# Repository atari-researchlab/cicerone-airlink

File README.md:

<!-- LICENSE INFORMATION
Copyright (C) 2025 ATARI Research Lab
Permission is granted to copy, distribute and/or modify this document
under the terms of the GNU Free Documentation License, Version 1.3
or any later version published by the Free Software Foundation;
with no Invariant Sections, no Front-Cover Texts, and no Back-Cover Texts.
A copy of the license is included in the section entitled "GNU
Free Documentation License".
-->

<!-- markdownlint-disable MD041 MD013 -->

<p align="center">
  Grant <strong><em>PID2021-126810OB-I00</em></strong> funded by:<br />
  <br />
</p>

<p align="center">

</p>

* * *

<!-- markdownlint-enable MD013 -->

# CICERONE AirLink

CICERONE AirLink© is an indoor air quality telemonitoring device designed for the project CICERONE
(*PID2021-126810OB-I00*).

The air quality device operates by transmitting data every ten minutes for all the parameters
collected by the various sensors, thanks to the communication module created in conjunction with the
RTC. This way, if there are no data transmission failures, a total of 144 daily data points are
obtained for each of the parameters collected by the CO2 and PM/VOCs sensors.

## Table of Contents

<!-- markdownlint-disable MD007 -->
- [CICERONE AirLink](#cicerone-airlink)
  - [Table of Contents](#table-of-contents)
  - [🎓 Features](#-features)
  - [📝 Specifications](#-specifications)
  - [📚 Documentation](#-documentation)
  - [📑 Citations](#-citations)
    - [APA](#apa)
    - [BibTeX](#bibtex)
  - [📃 Licences](#-licences)
<!-- markdownlint-enable MD007 -->

## 🎓 Features

- Sensors for measuring particulate matter (PM1, PM2.5, PM4, and PM10), volatile organic compounds
  (VOCs), carbon dioxide (CO2), temperature, and relative humidity.
- Clock for synchronizing sensor data readings and configuring the data packets to be transmitted.
- Autonomous data transmission independent of the user via an NB-IoT communication module. The
  device includes its own SIM card for sending average sensor values every ten minutes.
- Energy autonomy of up to 5 hours of operation on a fully charged battery.
- Optional cough detection feature using a machine learning algorithm. The device can count the
  number of cough events within a desired time frame.

[Back to top](#top)

## 📝 Specifications

- Electronics
    - Microcontroller
        - Arduino Nano 33 BLE Sense Rev2
    - Sensors
        - PM/VOC
        - CO2
        - Temperature
        - Ambient relative humidity
    - I/O
        - Power switch
    - Communication
        - NB-IoT module (SIM7020G)
    - Others
        - 2-layer custom PCB
        - RTC
        - 900 mAh Lithium-ion battery
        - 5V@1A AC-DC adapter
- Mechanics
    - 3D-printed case
    - Developed in SOLIDWORKS® 2020
- Firmware
    - Sends the data to a server containing 10 minutes average measurements of all sensors via the
      NB-IoT module.
    - Developed in Arduino IDE

[Back to top](#top)

## 📚 Documentation

- [Documentation](https://atari-researchlab.github.io/cicerone-airlink/)
- [Description](https://atari-researchlab.github.io/cicerone-airlink/description/)
    - [Electronics](https://atari-researchlab.github.io/cicerone-airlink/description/electronics/)
    - [Firmware](https://atari-researchlab.github.io/cicerone-airlink/description/firmware/)
- [User guide](https://atari-researchlab.github.io/cicerone-airlink/user-guide/)
    - [Assembly](https://atari-researchlab.github.io/cicerone-airlink/user-guide/assembly/)
    - [Firmware customization](https://atari-researchlab.github.io/cicerone-airlink/user-guide/firmware-configuration/)

[Back to top](#top)

## 📑 Citations

Please consider citing our papers in your publications if the project helps your research.

### APA

``` text
[1] Camacho-Magriñán, P.; Sales-Lerida, D.; León-Jiménez, A.; Sanchez-Morillo, D. Indoor
Environmental Monitoring and Chronic Respiratory Diseases: A Systematic Review. Technologies 2025,
13, 122. https://doi.org/10.3390/technologies13030122
```

``` text
[2] P. Camacho Magriñan, D. Sales Lerida, R. Moreno Mellado, A. Lara Doña, & D. Sánchez Morillo.
(2024). Sistema de telemonitorización de la calidad de aire interior para pacientes con EPOC. XLII
Congreso Anual de la Sociedad Española de Ingeniería Biomédica. CASEIB 2024, 89-92.
```

### BibTeX

``` bibtex
@Article{technologies13030122,
AUTHOR = {Camacho-Magriñán, Patricia and Sales-Lerida, Diego and León-Jiménez, Antonio and
Sanchez-Morillo, Daniel},
TITLE = {Indoor Environmental Monitoring and Chronic Respiratory Diseases: A Systematic Review},
JOURNAL = {Technologies},
VOLUME = {13},
YEAR = {2025},
NUMBER = {3},
ARTICLE-NUMBER = {122},
URL = {https://www.mdpi.com/2227-7080/13/3/122},
ISSN = {2227-7080},
DOI = {10.3390/technologies13030122}
}
```

``` bibtex
@inproceedings{6842c68c8a34bb2df9fc79a9,
title={Sistema de telemonitorización de la calidad de aire interior para pacientes con EPOC},
ISBN={978-84-09-67332-2},
booktitle={XLII Congreso Anual de la Sociedad Española de Ingeniería Biomédica. CASEIB 2024},
publisher={Sociedad Española de Ingeniería Biomédica (SEIB)},
author={P. Camacho Magriñan and D. Sales Lerida and R. Moreno Mellado and A. Lara Doña and D.
Sánchez Morillo},
year={2024},
pages={89-92}
}
```

[Back to top](#top)

## 📃 Licences

All hardware materials and designs, firmware and documentation provided here are licenced under the
following licenses:
<!-- markdownlint-disable MD013 -->
- Hardware: <a href="/hardware/LICENSE.md" target="_blank"> CERN Open Hardware Licence Version 2 - Strongly Reciprocal</a>
- Firmware source code: <a href="firmware/LICENSE.md" target="_blank"> GNU General Public License version 3 or later</a>
- Documentation: <a href="/docs/LICENSE.md" target="_blank"> GNU Free Documentation License, Version 1.3 or later</a>

[Back to top](#top)

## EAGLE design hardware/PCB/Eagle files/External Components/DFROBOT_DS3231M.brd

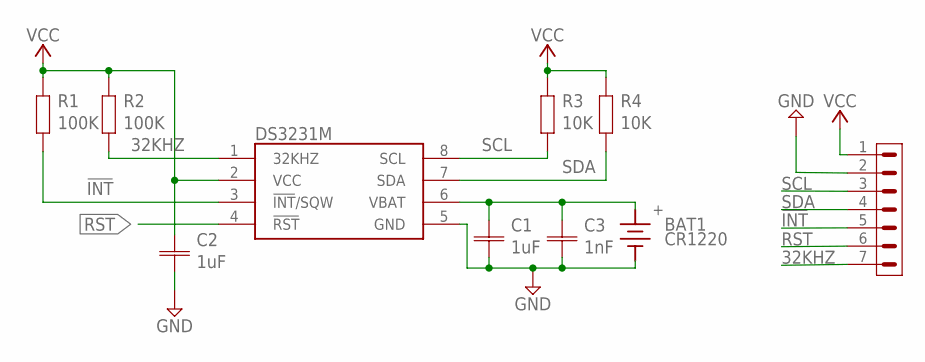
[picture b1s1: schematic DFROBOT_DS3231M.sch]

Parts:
BAT1: CR1220; S8411-45R
C1, C2: 1uF; CAPC1005X60
C3: 1nF; CAPC1005X60
DS3231M: DS3231MZ+; SOIC127P600X175-8N
JP1: PINHD-1X7; DS3231M_HEADER
R1, R2: 100K; RESC1005X40
R3, R4: 10K; RESC1005X40

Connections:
32KHZ: DS3231M.1 (32KHZ), JP1.7, R2.2
!INT: DS3231M.3 (!INT!/SQW), JP1.5, R1.2
GND: BAT1.1 (-), C1.2, C2.2, C3.2, DS3231M.5 (GND), JP1.2
RST: DS3231M.4 (!RST), JP1.6
SCL: DS3231M.8 (SCL), JP1.3, R3.2
SDA: DS3231M.7 (SDA), JP1.4, R4.2
VBAT: BAT1.2 (+), C1.1, C3.1, DS3231M.6 (VBAT)
VCC: C2.1, DS3231M.2 (VCC), JP1.1, R1.1, R2.1, R3.1, R4.1

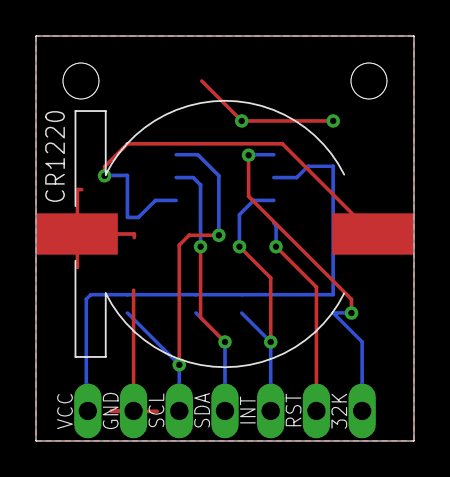
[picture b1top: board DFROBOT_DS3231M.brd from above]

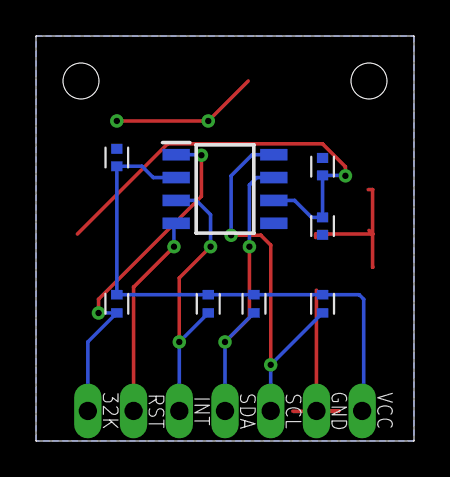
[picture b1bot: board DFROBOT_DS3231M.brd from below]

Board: 2 copper layers, 21.0 x 22.5 mm, 10 parts (8 on the bottom side), 8 nets.

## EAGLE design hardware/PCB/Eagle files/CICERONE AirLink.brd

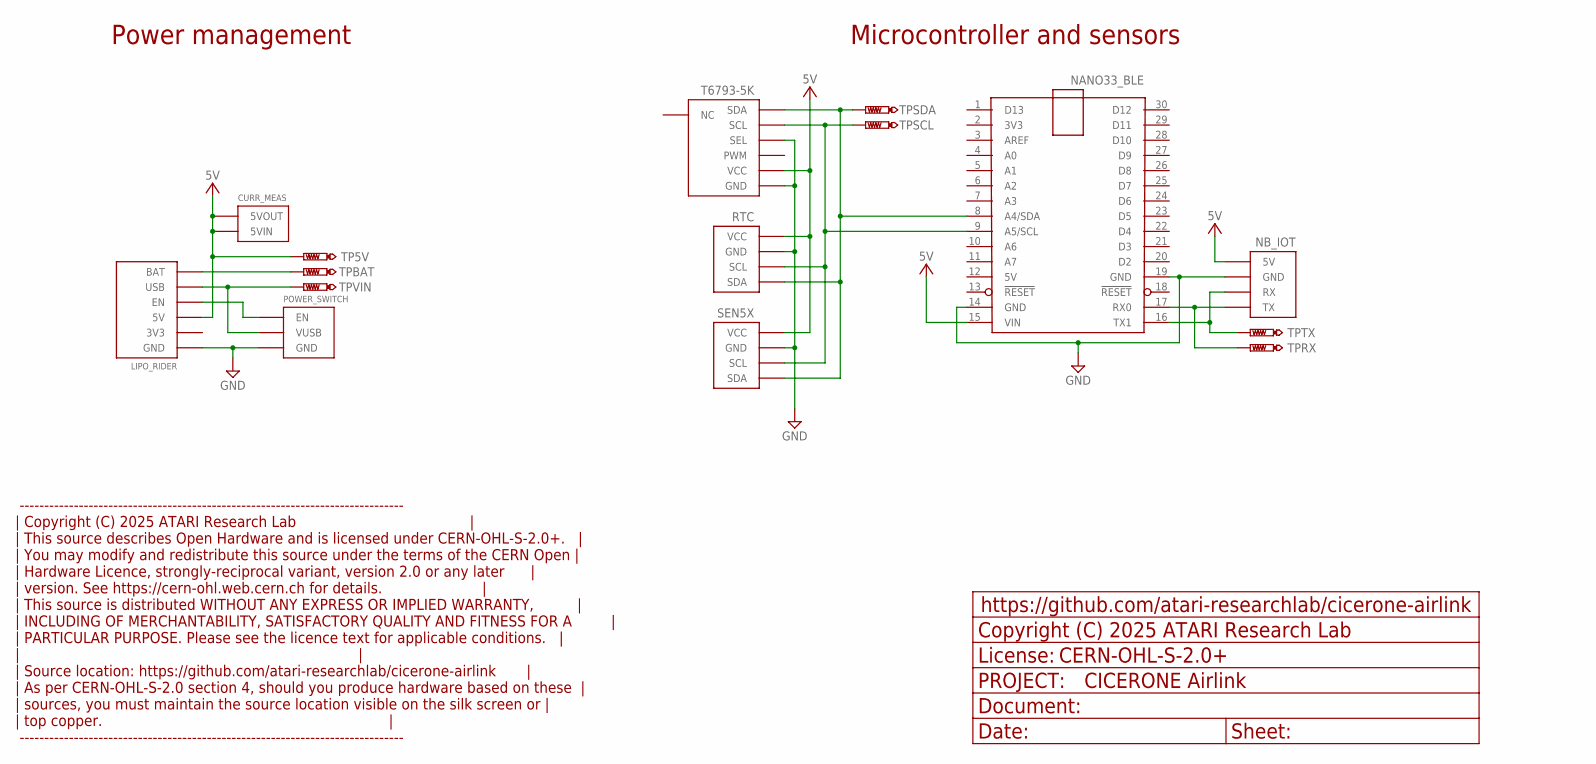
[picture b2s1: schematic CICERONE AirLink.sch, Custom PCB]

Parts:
CURR_MEAS: I→; PIN2X1
LIPO_RIDER: LIPO-RIDER; LIPO-RIDER-STAND
NANO33_BLE: NANO33_BLEPIN; NANO_BLE33_PIN
NB_IOT: GROVE-UARTSMD; GROVE_SMD
POWER_SWITCH: USB_SWITCH; USB-SWITCH
RTC: MODULO_RTC; DS3231M-MOD-90
SEN5X: I2C-HEADER
T6793-5K: T6793
TP5V: PTR1TP20SQ; TP20SQ
TPBAT: PTR1TP20SQ; TP20SQ
TPRX: PTR1TP20SQ; TP20SQ
TPSCL: PTR1TP20SQ; TP20SQ
TPSDA: PTR1TP20SQ; TP20SQ
TPTX: PTR1TP20SQ; TP20SQ
TPVIN: PTR1TP20SQ; TP20SQ

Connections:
5V: CURR_MEAS.P$1 (5VOUT), CURR_MEAS.P$2 (5VIN), LIPO_RIDER.P$4 (5V), NANO33_BLE.15 (VIN), NB_IOT.ROJ (5V), RTC.P$1 (VCC), SEN5X.VCC, T6793-5K.P$3 (VCC), TP5V.TP
EN: LIPO_RIDER.P$2 (EN), POWER_SWITCH.P$4 (EN)
GND: LIPO_RIDER.P$3 (GND), LIPO_RIDER.P$5 (GND), LIPO_RIDER.P$7 (GND), NANO33_BLE.14 (GND), NANO33_BLE.19 (GND), NB_IOT.NEG (GND), NB_IOT.P$1 (GND), NB_IOT.P$2 (GND), POWER_SWITCH.P$1 (GND), RTC.P$2 (GND), SEN5X.GND, T6793-5K.P$4 (GND), T6793-5K.P$6 (SEL)
RX_ARDU: NANO33_BLE.17 (RX0), NB_IOT.BLA (TX), TPRX.TP
SCL: NANO33_BLE.9 (A5/SCL), RTC.P$3 (SCL), SEN5X.SCL, T6793-5K.P$2 (SCL), TPSCL.TP
SDA: NANO33_BLE.8 (A4/SDA), RTC.P$4 (SDA), SEN5X.SDA, T6793-5K.P$1 (SDA), TPSDA.TP
TX_ARDU: NANO33_BLE.16 (TX1), NB_IOT.AMA (RX), TPTX.TP
VBAT: LIPO_RIDER.P$6 (BAT), TPBAT.TP
VUSB: LIPO_RIDER.P$8 (USB), POWER_SWITCH.P$2 (VUSB), POWER_SWITCH.P$3 (VUSB), TPVIN.TP

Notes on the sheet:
Power management
Microcontroller and sensors
------------------------------------------------------------------------------ | Copyright (C) 2025 ATARI Research Lab | | This source describes Open Hardware and is licensed under CERN-OHL-S-2.0+. | | You may modify and redistribute this source under the terms of the CERN Open | | Hardware Licence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

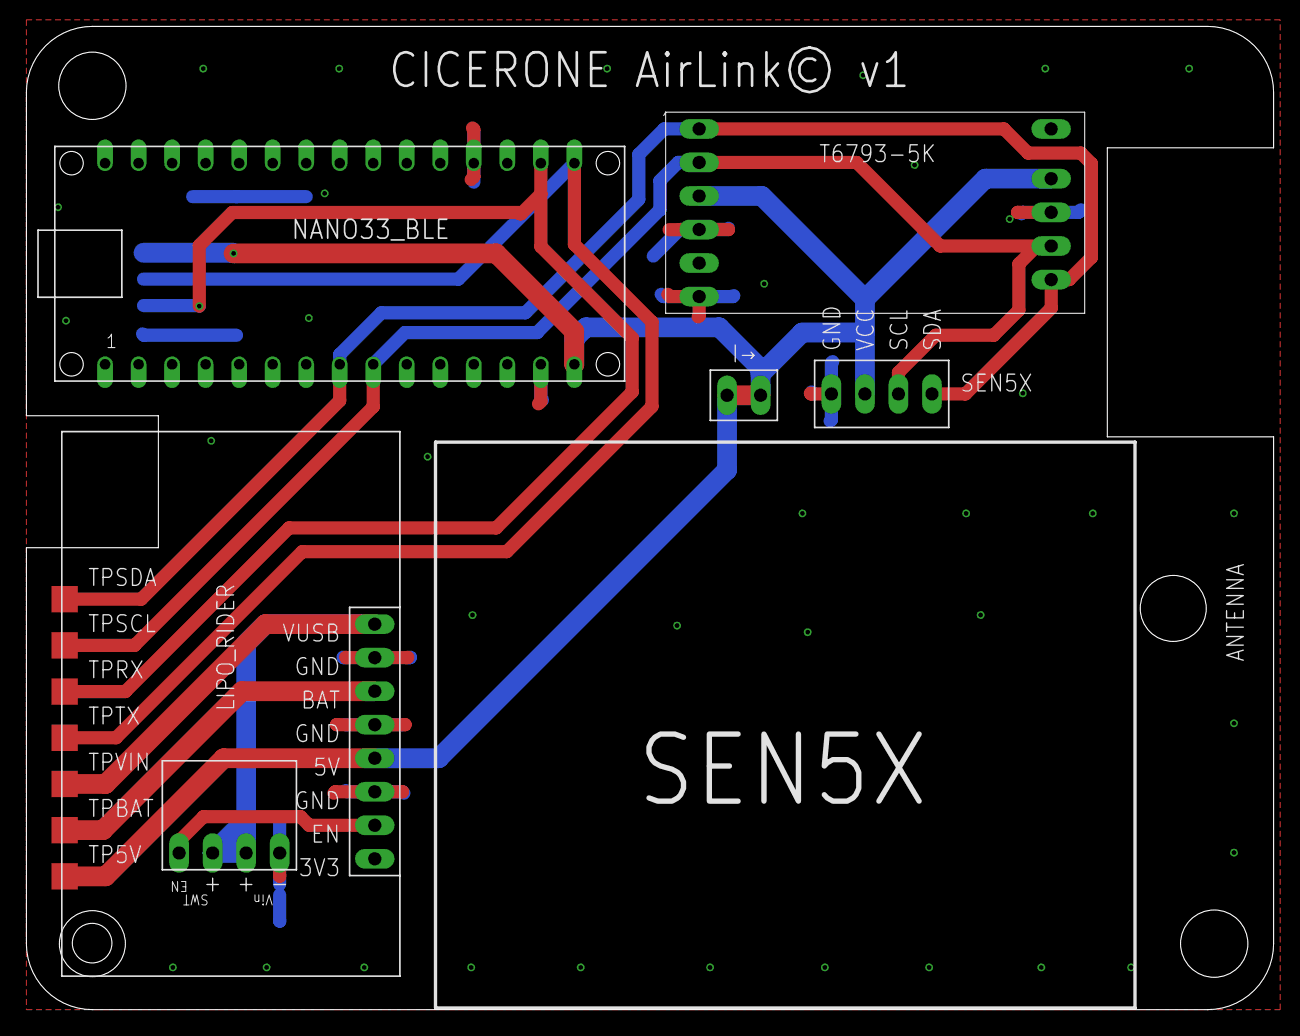
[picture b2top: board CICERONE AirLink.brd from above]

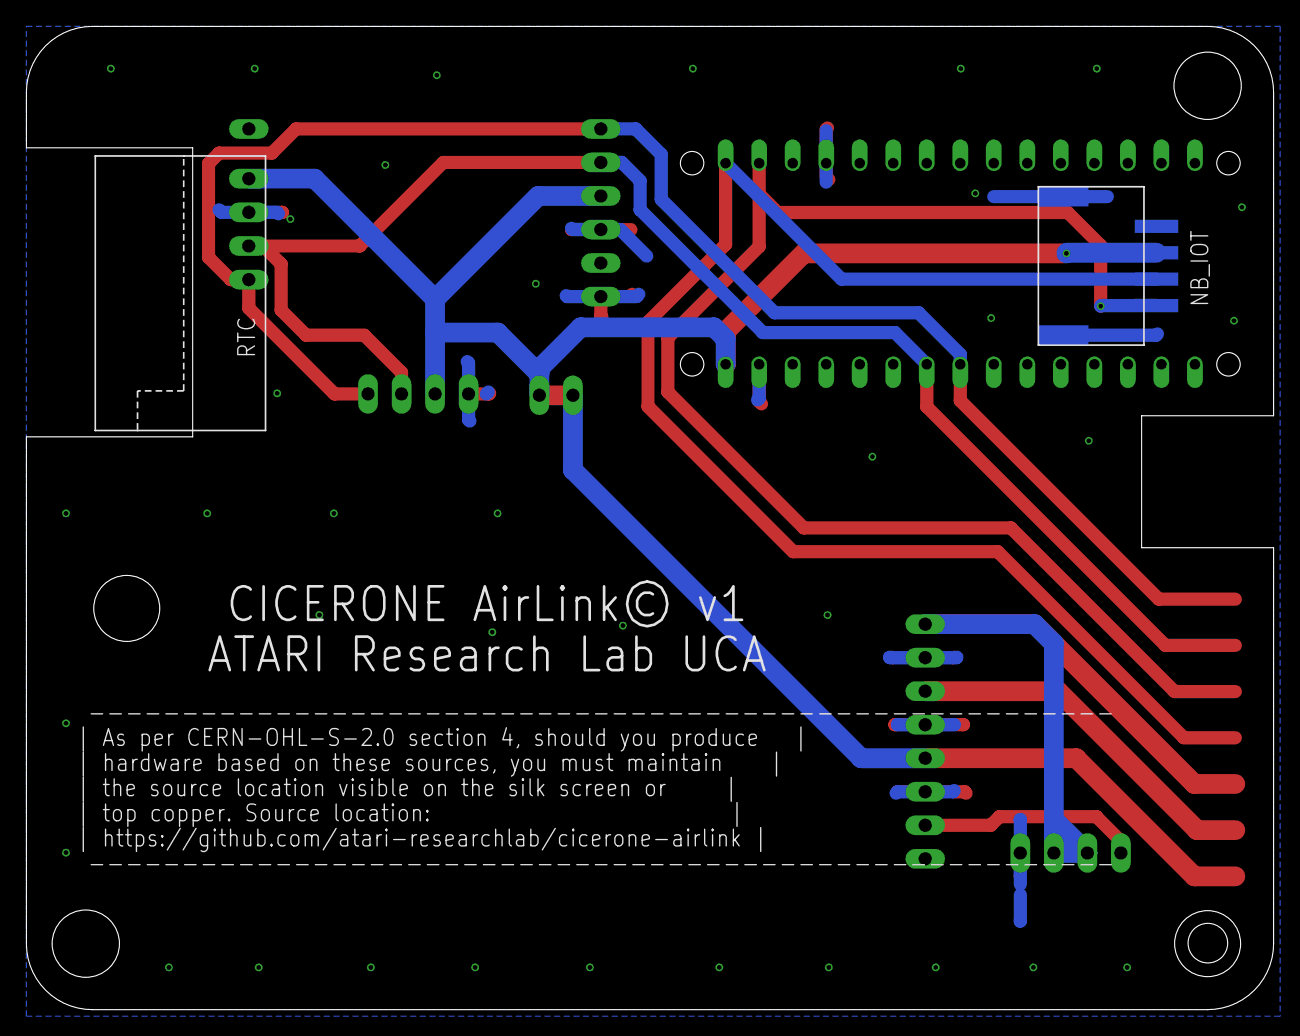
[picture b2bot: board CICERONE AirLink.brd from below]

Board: 2 copper layers, 94.5 x 74.5 mm, 15 parts (2 on the bottom side), 9 nets.

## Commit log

2025-07-28 Documentation with MkDocs
2025-07-28 Add Airlink exploded and PCB images
    Added two new images to the documentation: an exploded view and a PCB view of the Cicerone Airlink. These images will help clarify hardware details for users and developers.
2025-07-29 Fix image path in navigation, update license description, enhance firmware documentation with state diagrams, and configure MkDocs for Mermaid support.
2025-07-29 Fix image path in navigation footer
2025-07-29 Update license in firmware documentation
    Replaced the GNU Free Documentation License with the GNU General Public License v3 in docs/about/lic-firmware.md to accurately reflect the licensing of firmware. Added license information headers to 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
2025-07-30 Update mkdocs.yml to fix site URL, enhance navigation features, and correct language links
2025-07-30 Add micin-uefeder-aei-sidebar image and fix image path in navigation
2025-07-30 Fix image path for micin-uefeder-aei-sidebar and add missing image file
2025-07-30 Update AirLink PCB to v57 and refresh hardware files
    Renamed and updated PCB assembly and drawing files to version 57, replaced outdated PDF and added new schematic and board files. Updated Gerber, drill, and ODB files, refreshed image assets, and fixe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
2025-07-31 Add authorship documentation and update citation formats in README and citations
2025-07-31 Fix citation formatting in README for improved clarity
2025-07-31 Deployed 0333179 with MkDocs version: 1.6.1
2025-08-08 Deployed d3b3285 with MkDocs version: 1.6.1
2025-08-14 Update authorship details and add CITATION.cff file for improved documentation
2025-08-15 Restructure firmware directory and add Doxyfile
    Moved and renamed firmware source/header files from firmware/Airlink/ to firmware/, updating references accordingly. Added Doxyfile for Doxygen documentation generation and updated .gitignore to excl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
2025-08-15 Refactor sensor APIs and update Doxygen config
    Improved documentation and comments for DS3231M, SEN5X, and T6793 sensor APIs. Updated debug messages and logging levels for better clarity. Removed redundant license and reference blocks from header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
2025-08-16 updated hardware files
2025-08-21 Add Arduino.h includes and fix format specifiers
    Added #include <Arduino.h> to multiple header files for compatibility. Fixed format specifiers in DEBUG_INFO and DEBUG_VERBOSE calls for correct data types. Removed unused variables and functions, an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
2025-08-21 Refactor Doxygen config and update .gitignore
    Moved Doxyfile and DoxygenLayout.xml to .doxygen directory and updated paths to use relative references for portability. Enhanced .gitignore to better handle build artifacts, logs, and temporary file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
2025-08-21 Add VSCode config and generated firmware docs
    Added initial .vscode configuration files for Arduino development. Generated firmware documentation files were added under docs/firmware/html, and the Doxygen configuration file was moved to the proj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
2025-08-23 Refactor docs, config, and assets structure
    Moved and renamed documentation files for improved organization, updated Doxyfile and CI workflow for mkdoxy integration, added markdownlint config, and enhanced VSCode and YAML settings. Documentati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
2025-10-15 Refactor and update documentation across firmware
    Updated and standardized file headers, comments, and documentation in multiple firmware source and header files for improved clarity and maintainability. Adjusted configuration values and macro usage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
2025-10-15 Update config files for markdownlint, VSCode, and mkdocs
    Changed markdownlint indentation from 4 to 2 spaces. Commented out mkdoxy and reference section entries in mkdocs.yml, and added mkdocstrings configuration comments.
2025-10-15 docs: configure dual-language API documentation system
    - Add Doxyfile_es for Spanish firmware documentation (firmware_es/)
    - Rename Doxyfile to Doxyfile_en for English firmware documentation
    - Integrate mkdoxy plugin in mkdocs.yml with bilingual support:
    * es/firmware project → firmware_es/ source directory
    * firmware project → firmware/ source directory
    * Configure FILE_PATTERNS, RECURSIVE, EXTRACT_ALL, EXCLUDE settings
2025-10-15 fix: update excluded firmware documentation files in mkdocs configuration
2025-10-15 fix: update firmware documentation exclusions in mkdocs configuration
2025-10-16 docs: enhance documentation with complete user guides
    docs: enhance documentation with complete user guides
    Add comprehensive guides for firmware configuration, debug system, and architecture. Enhance AUTHORS.md with CRediT taxonomy and contribution matrix. Create CONTRIBUTING.md with detailed guidelines. 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
2025-10-16 fix: update mkdocs CI workflow to include mkdocs-awesome-nav
2025-10-16 docs(firmware): reorganize documentation into modular structure
    Split firmware/index.md into 4 specialized documents (architecture,
    program-flow, sensor-interfaces, data-transmission) plus concise
    landing page with Material MkDocs navigation cards.
    - Add firmware documentation modules (320-569 lines each)
    - Transform index.md into navigation hub (234 lines)
    - Add .nav.yml files for firmware/ and user-guide/
2025-10-16 docs: fix typos and standardize battery specifications
    - Fix typos: "Comunication", "Seed Studio", "a embedded"
    - Unify battery life to "~5 hours" (was "4-6 hours" in firmware docs)
    - Standardize battery format to "900 mAh" with space
2025-10-17 docs: update BOM table and fix typos across documentation
    - Update component cost table in other-information.md with official BOM data
    - Add missing components: standoff, rocker switch, cable gland
    - Fix typos: 'Comunication' → 'Communication' in README.md
    - Fix typos: 'Seed Studio' → 'Seeed Studio' in electronics.md
    - Fix grammar: 'a embedded' → 'an embedded' in description/index.md
    - Standardize battery life to '~5 hours' across all documentation
2025-10-17 fix: assembly images
2025-10-20 fix: update image paths in assembly documentation
2025-10-21 fix: renamed assembly images for documentation
2025-10-21 chore: force redeploy for image cache refresh
2025-10-21 fix: update .gitignore and improve formatting in CONTRIBUTING.md
2025-10-21 fix(ci): enable Git LFS support in mkdocs deployment workflow
    - Add lfs: true to checkout action
    - Add explicit git lfs pull step
    - Fixes assembly images showing as 131-byte LFS pointers instead of actual images
    - Resolves 404/broken image issues on GitHub Pages
2025-10-22 feat: add release notes for v2.0.0 and update citation for Zenodo
2025-10-22 fix: CITATION.cff for Zenodo
2025-10-22 fix: remove unnecessary comments and versioning details from CITATION.cff
2025-10-23 Deployed bbd10e5 with MkDocs version: 1.6.1

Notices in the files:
hardware/PCB/Eagle files/CICERONE AirLink.brd:
As per CERN-OHL-S-2.0 section 4, should you produce
hardware/PCB/Eagle files/CICERONE AirLink.sch:
COPYRIGHT: Copyright (C) 2025 ATARI Research Lab
LICENSE: CERN-OHL-S-2.0+
Hardware Licence, strongly-reciprocal variant, version 2.0 or any later
version. See https://cern-ohl.web.cern.ch for details.
PARTICULAR PURPOSE. Please see the licence text for applicable conditions.
As per CERN-OHL-S-2.0 section 4, should you produce hardware based on these
